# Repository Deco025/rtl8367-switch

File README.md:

# RTL8367 Switch

**RTL8367RB 五口千兆非网管交换机**

> An open-source five-port gigabit Ethernet switch built around the Realtek RTL8367RB. It is unmanaged: the
> chip boots from strap pins and needs no MCU. Each port has a discrete Pulse H5007NL magnetics module, a shielded RJ45
> and two status LEDs. A 12 V input feeds two on-board bucks, 3.3 V (TPS54331) and 1.1 V (TPS62130A).
> The board is a compact 100 × 72 mm, 4-layer KiCad 10 design, assembled on both sides, with complete fabrication
> outputs.

| 正面（网口一侧） | 背面（电源一侧） |
|---|---|
|  |  |

### PCB 走线

| 顶层 F.Cu | 底层 B.Cu（从背面看） |
|---|---|
|  |  |

第 2 层整层是地，第 3 层是电源分区；图里只画了两个外层。

### 前代样机

这是本设计的前代样机，已经搭建并通电运行，图中两个网口接线后链路灯亮起。v0.1 在它的基础上重新设计，网络变压器从 JXD G2401S 换成了 Pulse H5007NL。上面的渲染图和走线图都是 v0.1。

---

## 目录

- [主要指标](#主要指标)
- [系统结构](#系统结构)
- [仓库结构](#仓库结构)
- [打开工程](#打开工程)
- [打样与装配](#打样与装配)
- [设计要点](#设计要点)
- [设计检查与装配注意事项](#设计检查与装配注意事项)
- [许可证](#许可证)
- [致谢](#致谢)

## 主要指标

| 项 | 值 |
|---|---|
| 交换芯片 | Realtek RTL8367RB-VB-CG（LQFP-128，带散热焊盘） |
| 端口 | 5 × 10/100/1000BASE-T，RJ45 带屏蔽壳 |
| 管理 | 非网管，靠 strap 引脚配置；预留 SMI 调试口（J251）和 EEPROM 位置（默认不贴） |
| 网络变压器 | Pulse H5007NL × 5（每口一颗，分立） |
| 指示灯 | 每口一绿一黄，外加一颗电源灯 |
| 输入 | 12 V DC，5.5 × 2.1 mm 插座（CUI PJ-102AH） |
| 输入保护 | 自恢复保险丝 0.75 A（1812L075/33DR）、防反接肖特基 SS34、TVS SMBJ15A |
| 3.3 V | TPS54331 降压，6.8 µH，SS34 续流 |
| 1.1 V（芯片核心） | TPS62130A 降压，2.2 µH，放在背面，紧靠芯片 |
| 复位 | TPS3808G30 监控 3.3 V，带手动复位按键 |
| 时钟 | 25 MHz 晶体 |
| PCB | 100 × 72 mm，4 层，1.58 mm，嘉立创叠层 JLC04161H-3313A（外层 1 oz，内层 0.5 oz） |
| 装配 | 双面贴片：正面 56 个、背面 129 个，共 185 个 |

## 系统结构

```mermaid
flowchart LR
    DC[12 V 输入<br/>保险丝 · 防反接 · TVS] --> B1[TPS54331<br/>3.3 V]
    B1 --> B2[TPS62130A<br/>1.1 V 核心]
    B1 --> FB[磁珠滤波<br/>3.3 V / 1.1 V 模拟与 PLL]
    B1 --> RST[TPS3808<br/>复位监控]
    B2 --> SW
    FB --> SW
    RST --> SW
    X[25 MHz 晶体] --> SW[RTL8367RB<br/>5 口千兆交换]
    SW -- MDI × 4 对 --> T[H5007NL × 5<br/>网络变压器]
    T --> J[RJ45 × 5<br/>Bob Smith 终端到 CHASSIS]
    SW --> LED[LED × 10]
```

- 5 个网口都用芯片内置的 PHY，MDI 从芯片直连变压器，中间没有其他器件。
- 变压器芯片侧的中心抽头各接 0.1 µF 到地，另外预留一个 0 Ω 到 +3V3A 的位置（默认不贴）。
- 线缆侧中心抽头各经 75 Ω 汇到一点，再经 1 nF / 2 kV 接屏蔽地 CHASSIS（Bob Smith 终端）。CHASSIS 与 GND 之间有一颗 1 nF 电容。
- 每对差分线旁预留了 ESD 保护（TPD4E02B04，默认不贴）。

更完整的说明见 [docs/design.md](docs/design.md)。

## 仓库结构

```
.
├── rtl8367-switch.kicad_pro   KiCad 工程
├── *.kicad_sch                原理图：根页 + 电源、芯片供电、芯片控制、5 个网口
├── rtl8367-switch.kicad_pcb   PCB
├── lib/                       工程自带的符号和封装（RTL8367RB、H5007NL、RJ45）
├── fab/                       生产文件（Gerber zip、BOM、坐标、装配图、DRC 报告）
├── 3dmodels/                  第三方 3D 模型的来源清单（模型文件不随仓库分发）
├── docs/
│   ├── design.md              设计说明
│   └── schematics/            原理图 PDF（不装 KiCad 也能看）
├── images/                    渲染图和走线图
├── CHANGELOG.md
└── LICENSE                    CERN-OHL-S-2.0
```

## 打开工程

1. 安装 [KiCad](https://www.kicad.org/) **10.0** 或更新版本。
2. 打开 `rtl8367-switch.kicad_pro`。RTL8367RB、H5007NL 和 RJ45 的符号与封装在 `lib/` 里，工程的库表已经指向它们；其余来自 KiCad 官方库。
3. **3D 模型（可选）**：有 6 种器件的 3D 模型不在 KiCad 官方库里，版权也不允许随仓库再分发。按 [3dmodels/README.md](3dmodels/README.md) 下载到 `3dmodels/`，3D 查看器（`Alt+3`）里就能看到完整外观。不下载也不影响原理图、PCB 和生产文件。

## 打样与装配

生产文件已经导出好，坐标原点在板的左上角：

| 用途 | 文件 |
|---|---|
| 上传给板厂 | [`fab/rtl8367-switch-gerber.zip`](fab/rtl8367-switch-gerber.zip) |
| 物料清单 | [`fab/rtl8367-switch-bom.csv`](fab/rtl8367-switch-bom.csv) |
| 贴片坐标（两面） | [`fab/rtl8367-switch-pos.csv`](fab/rtl8367-switch-pos.csv) |
| 装配图（第 1 页正面，第 2 页背面镜像） | [`fab/rtl8367-switch-assembly.pdf`](fab/rtl8367-switch-assembly.pdf) |
| 下单参数 | [`fab/README.md`](fab/README.md) |

下单要点：

- 4 层，1.6 mm，FR4，**叠层选 JLC04161H-3313A**。差分线的线宽线距是按这个叠层算的 100 Ω，换叠层要重算。
- 最小线宽 / 线距 0.2 / 0.15 mm，过孔 0.45 / 0.3 mm 和 0.6 / 0.3 mm。U102 封装自带 0.2 mm 的散热孔，请确认板厂能做。
- 双面贴片，背面也有器件（大多是去耦电容和上下拉电阻）。
- 变压器之后（线缆侧）的地和电源平面是有意挖空的，保证隔离间距，不要让板厂“补铜”。
- 为了版面整洁，丝印上放不下的一些小阻容位号只保留在装配层（Fab），焊接时请对照装配图。

## 设计要点

- **MDI 直通**：变压器的通道在原理图里重新分配过，芯片到变压器的 20 对差分线全部在顶层直走，不打孔、不交叉，下面是完整的地层。线对的顺序和极性调整放在变压器之后、网口下方那一小段。千兆和 10M 模式下，芯片会自动纠正极性；100M 模式对极性不敏感。
- **电源分区**：第 3 层在芯片下方分成 1.1 V 核心、1.1 V 模拟、3.3 V 模拟几块，其余是 3.3 V 主电源；1.1 V PLL 经磁珠单独供电。每个电源脚旁打一个过孔，直通背面的去耦电容。
- **两个降压电源分开放**：3.3 V 在正面右后角，开关节点铜皮只包芯片 SW 脚、续流二极管和电感，离最近的差分线约 4.6 mm；1.1 V 在背面，紧挨芯片，输入环路（PVIN–C112–PGND）在背面就地闭合，输出经过孔直接进第 3 层的核心电源区。两路的反馈分压器和各自的开关节点之间都隔着两层平面。
- **隔离与屏蔽**：变压器之后（线缆侧）不铺地和电源平面，四个线对分走四层，和芯片侧之间留隔离带；网口屏蔽壳和 Bob Smith 终端单独接 CHASSIS 铺铜。外层地铺铜与差分线保持间距，并用缝合过孔连到地层。

详见 [docs/design.md](docs/design.md)。

## 设计检查与装配注意事项

原理图 ERC 0，PCB DRC 0 错误、0 未连接，原理图与 PCB 一致。装配和调试时请留意：

1. **芯片侧中心抽头**：默认每个抽头接 0.1 µF 到地，同时预留了接 +3V3A 的 0 Ω 位置（接法参考同厂 RTL8211E 的布局指南），可按需要切换。
2. **默认转发配置和 LED 功能**由 strap 决定，可以通过 J251 的 SMI 口读写寄存器确认和调整。
3. **RJ45 的 1 脚方向**请在焊接前对照实物核对。
4. **绿色 LED** 正向压降约 2.8 V，470 Ω 限流下约 1 mA；想要更亮可以减小限流电阻。
5. **复位门限**为 2.79 V，偏低的门限用于避免上电时卡在复位里。
6. **DC 插座**（CUI PJ-102AH）请在下单前按厂家规格书确认货源和额定值。

欢迎提交 Issue 反馈问题或改进建议。

## 许可证

本项目的硬件设计文件（原理图、PCB、生产文件、文档）采用
**[CERN Open Hardware Licence Version 2 – Strongly Reciprocal (CERN-OHL-S-2.0)](LICENSE)**。

简单说：可以自由使用、学习、修改、生产和销售；但如果你发布修改后的设计，或者销售基于它的产品，必须用同样的许可证公开对应的设计源文件。

第三方封装、符号和 3D 模型各自遵循其原始许可，不在本许可证范围内。

## 致谢

- [KiCad](https://www.kicad.org/) 及其官方符号 / 封装 / 3D 库。
- 器件 3D 模型的来源见 [3dmodels/SOURCES.md](3dmodels/SOURCES.md)。

欢迎通过 Issue 反馈问题或提出改进。

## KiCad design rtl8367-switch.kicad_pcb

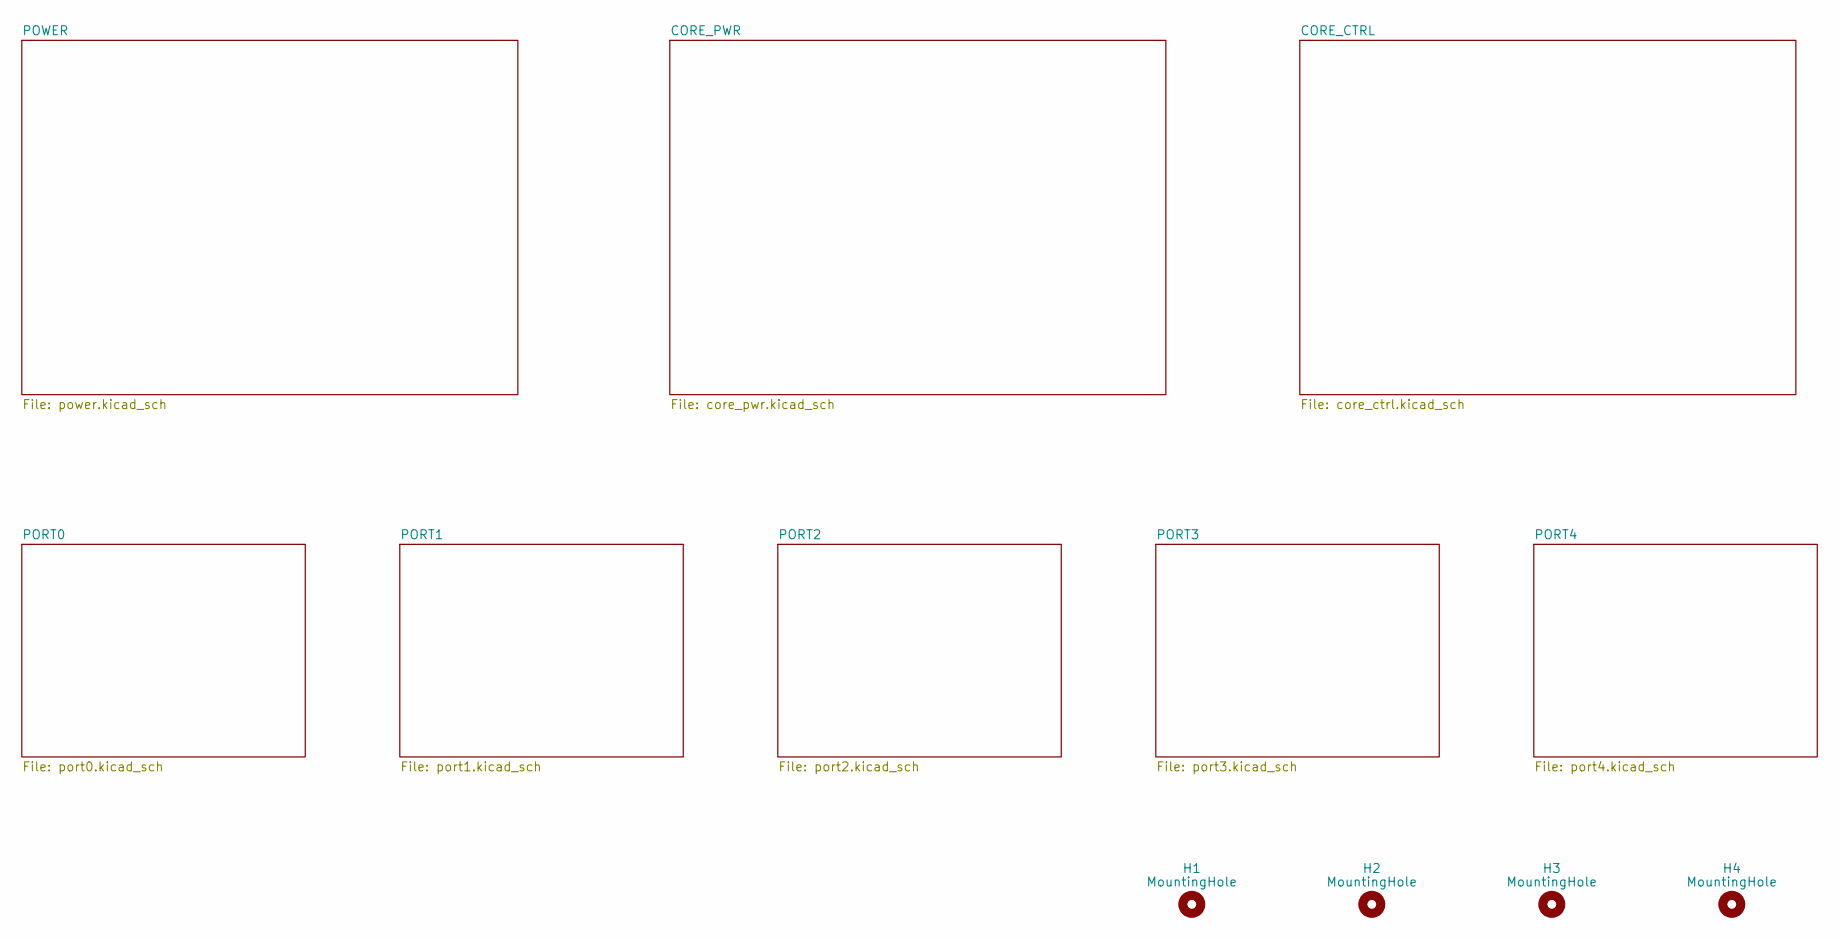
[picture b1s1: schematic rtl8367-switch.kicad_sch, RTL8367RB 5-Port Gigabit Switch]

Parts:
H1, H2, H3, H4: MountingHole; MountingHole_3.2mm_M3

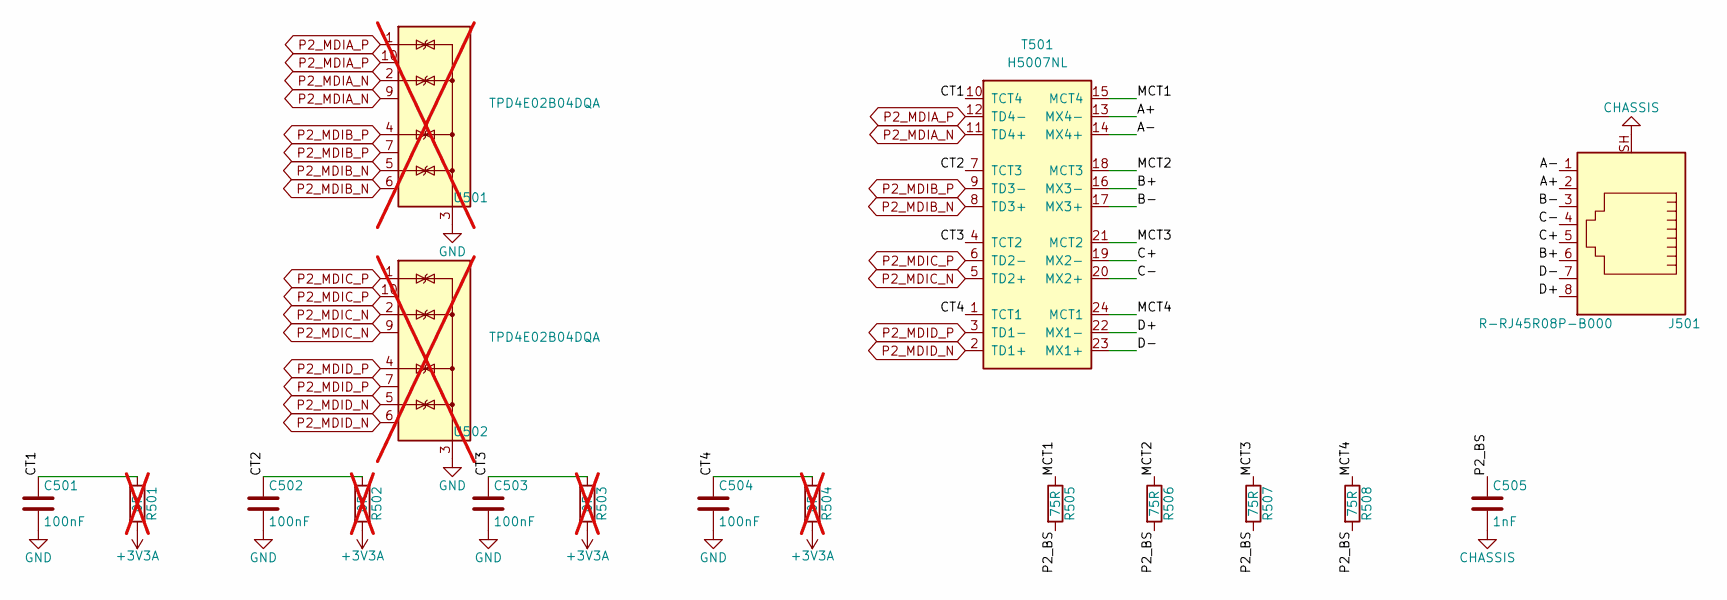
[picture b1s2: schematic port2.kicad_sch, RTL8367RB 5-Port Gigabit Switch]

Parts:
C501, C502, C503, C504: 100nF; C_0402_1005Metric; Voltage 16V
C505: 1nF; C_1206_3216Metric; Voltage 2kV
J501: R-RJ45R08P-B000; RJ45_Ckmtw_R-RJ45R08P-B000_Horizontal; MPN R-RJ45R08P-B000; LCSC C386756
R501, R502, R503, R504: 0R; R_0402_1005Metric; not fitted
R505, R506, R507, R508: 75R; R_0603_1608Metric; Tolerance 1%
T501: H5007NL; Pulse_H5007NL; MPN H5007NL; LCSC C6384935
U501, U502: TPD4E02B04DQA; USON-10_2.5x1.0mm_P0.5mm; MPN TPD4E02B04DQAR; not fitted

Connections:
+3V3A: R501.2, R502.2, R503.2, R504.2; also elsewhere on the board
/PORT2/A+: J501.2, T501.13 (MX4-)
/PORT2/A-: J501.1, T501.14 (MX4+)
/PORT2/B+: J501.6, T501.16 (MX3-)
/PORT2/B-: J501.3, T501.17 (MX3+)
/PORT2/C+: J501.5, T501.19 (MX2-)
/PORT2/C-: J501.4, T501.20 (MX2+)
/PORT2/CT1: C501.1, R501.1, T501.10 (TCT4)
/PORT2/CT2: C502.1, R502.1, T501.7 (TCT3)
/PORT2/CT3: C503.1, R503.1, T501.4 (TCT2)
/PORT2/CT4: C504.1, R504.1, T501.1 (TCT1)
/PORT2/D+: J501.8, T501.22 (MX1-)
/PORT2/D-: J501.7, T501.23 (MX1+)
/PORT2/MCT1: R505.1, T501.15 (MCT4)
/PORT2/MCT2: R506.1, T501.18 (MCT3)
/PORT2/MCT3: R507.1, T501.21 (MCT2)
/PORT2/MCT4: R508.1, T501.24 (MCT1)
/PORT2/P2_BS: C505.1, R505.2, R506.2, R507.2, R508.2
CHASSIS: C505.2, J501.SH; also elsewhere on the board
GND: C501.2, C502.2, C503.2, C504.2, U501.3 (G), U501.8 (G), U502.3 (G), U502.8 (G); also elsewhere on the board
P2_MDIA_N: T501.11 (TD4+), U501.2 (IO2), U501.9 (NC); also elsewhere on the board
P2_MDIA_P: T501.12 (TD4-), U501.1 (IO1), U501.10 (NC); also elsewhere on the board
P2_MDIB_N: T501.8 (TD3+), U501.5 (IO4), U501.6 (NC); also elsewhere on the board
P2_MDIB_P: T501.9 (TD3-), U501.4 (IO3), U501.7 (NC); also elsewhere on the board
P2_MDIC_N: T501.5 (TD2+), U502.2 (IO2), U502.9 (NC); also elsewhere on the board
P2_MDIC_P: T501.6 (TD2-), U502.1 (IO1), U502.10 (NC); also elsewhere on the board
P2_MDID_N: T501.2 (TD1+), U502.5 (IO4), U502.6 (NC); also elsewhere on the board
P2_MDID_P: T501.3 (TD1-), U502.4 (IO3), U502.7 (NC); also elsewhere on the board

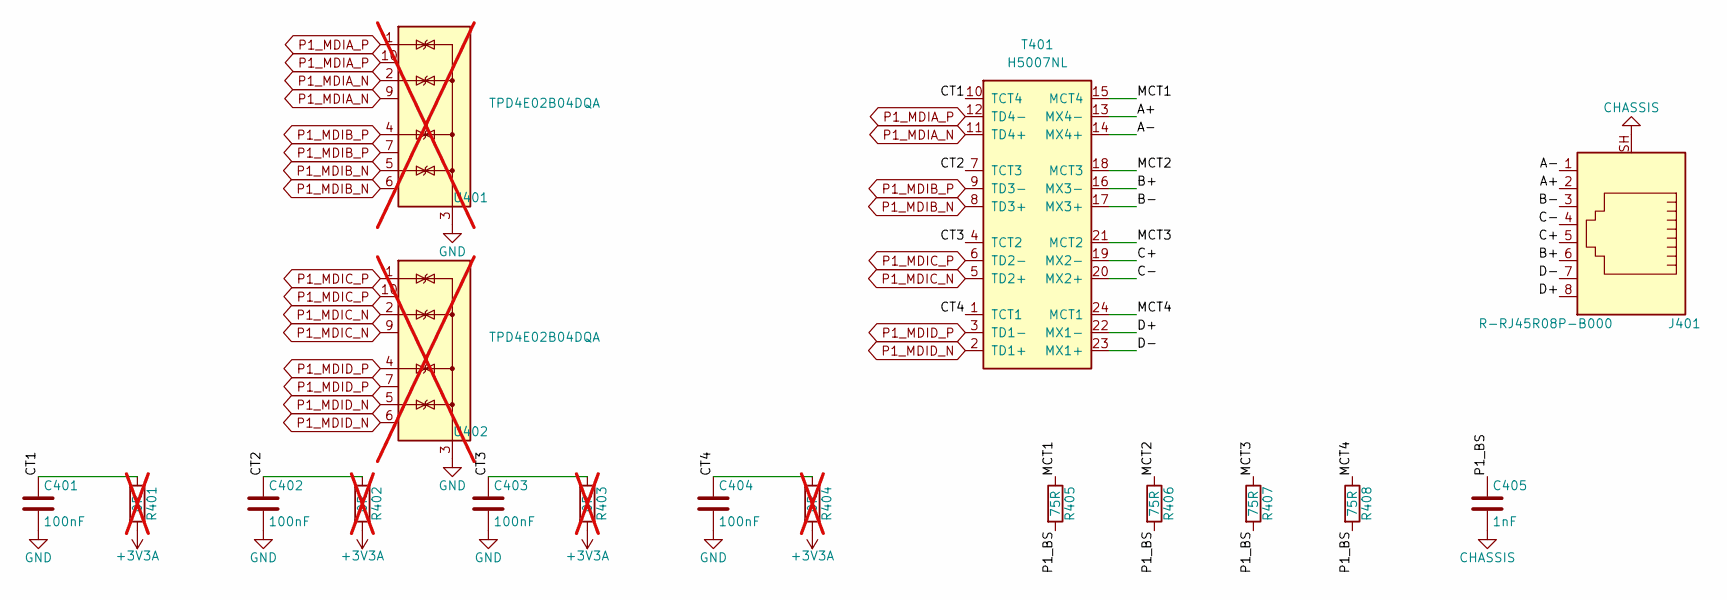
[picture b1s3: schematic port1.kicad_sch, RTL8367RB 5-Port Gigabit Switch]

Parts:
C401, C402, C403, C404: 100nF; C_0402_1005Metric; Voltage 16V
C405: 1nF; C_1206_3216Metric; Voltage 2kV
J401: R-RJ45R08P-B000; RJ45_Ckmtw_R-RJ45R08P-B000_Horizontal; MPN R-RJ45R08P-B000; LCSC C386756
R401, R402, R403, R404: 0R; R_0402_1005Metric; not fitted
R405, R406, R407, R408: 75R; R_0603_1608Metric; Tolerance 1%
T401: H5007NL; Pulse_H5007NL; MPN H5007NL; LCSC C6384935
U401, U402: TPD4E02B04DQA; USON-10_2.5x1.0mm_P0.5mm; MPN TPD4E02B04DQAR; not fitted

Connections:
+3V3A: R401.2, R402.2, R403.2, R404.2; also elsewhere on the board
/PORT1/A+: J401.2, T401.13 (MX4-)
/PORT1/A-: J401.1, T401.14 (MX4+)
/PORT1/B+: J401.6, T401.16 (MX3-)
/PORT1/B-: J401.3, T401.17 (MX3+)
/PORT1/C+: J401.5, T401.19 (MX2-)
/PORT1/C-: J401.4, T401.20 (MX2+)
/PORT1/CT1: C401.1, R401.1, T401.10 (TCT4)
/PORT1/CT2: C402.1, R402.1, T401.7 (TCT3)
/PORT1/CT3: C403.1, R403.1, T401.4 (TCT2)
/PORT1/CT4: C404.1, R404.1, T401.1 (TCT1)
/PORT1/D+: J401.8, T401.22 (MX1-)
/PORT1/D-: J401.7, T401.23 (MX1+)
/PORT1/MCT1: R405.1, T401.15 (MCT4)
/PORT1/MCT2: R406.1, T401.18 (MCT3)
/PORT1/MCT3: R407.1, T401.21 (MCT2)
/PORT1/MCT4: R408.1, T401.24 (MCT1)
/PORT1/P1_BS: C405.1, R405.2, R406.2, R407.2, R408.2
CHASSIS: C405.2, J401.SH; also elsewhere on the board
GND: C401.2, C402.2, C403.2, C404.2, U401.3 (G), U401.8 (G), U402.3 (G), U402.8 (G); also elsewhere on the board
P1_MDIA_N: T401.11 (TD4+), U401.2 (IO2), U401.9 (NC); also elsewhere on the board
P1_MDIA_P: T401.12 (TD4-), U401.1 (IO1), U401.10 (NC); also elsewhere on the board
P1_MDIB_N: T401.8 (TD3+), U401.5 (IO4), U401.6 (NC); also elsewhere on the board
P1_MDIB_P: T401.9 (TD3-), U401.4 (IO3), U401.7 (NC); also elsewhere on the board
P1_MDIC_N: T401.5 (TD2+), U402.2 (IO2), U402.9 (NC); also elsewhere on the board
P1_MDIC_P: T401.6 (TD2-), U402.1 (IO1), U402.10 (NC); also elsewhere on the board
P1_MDID_N: T401.2 (TD1+), U402.5 (IO4), U402.6 (NC); also elsewhere on the board
P1_MDID_P: T401.3 (TD1-), U402.4 (IO3), U402.7 (NC); also elsewhere on the board

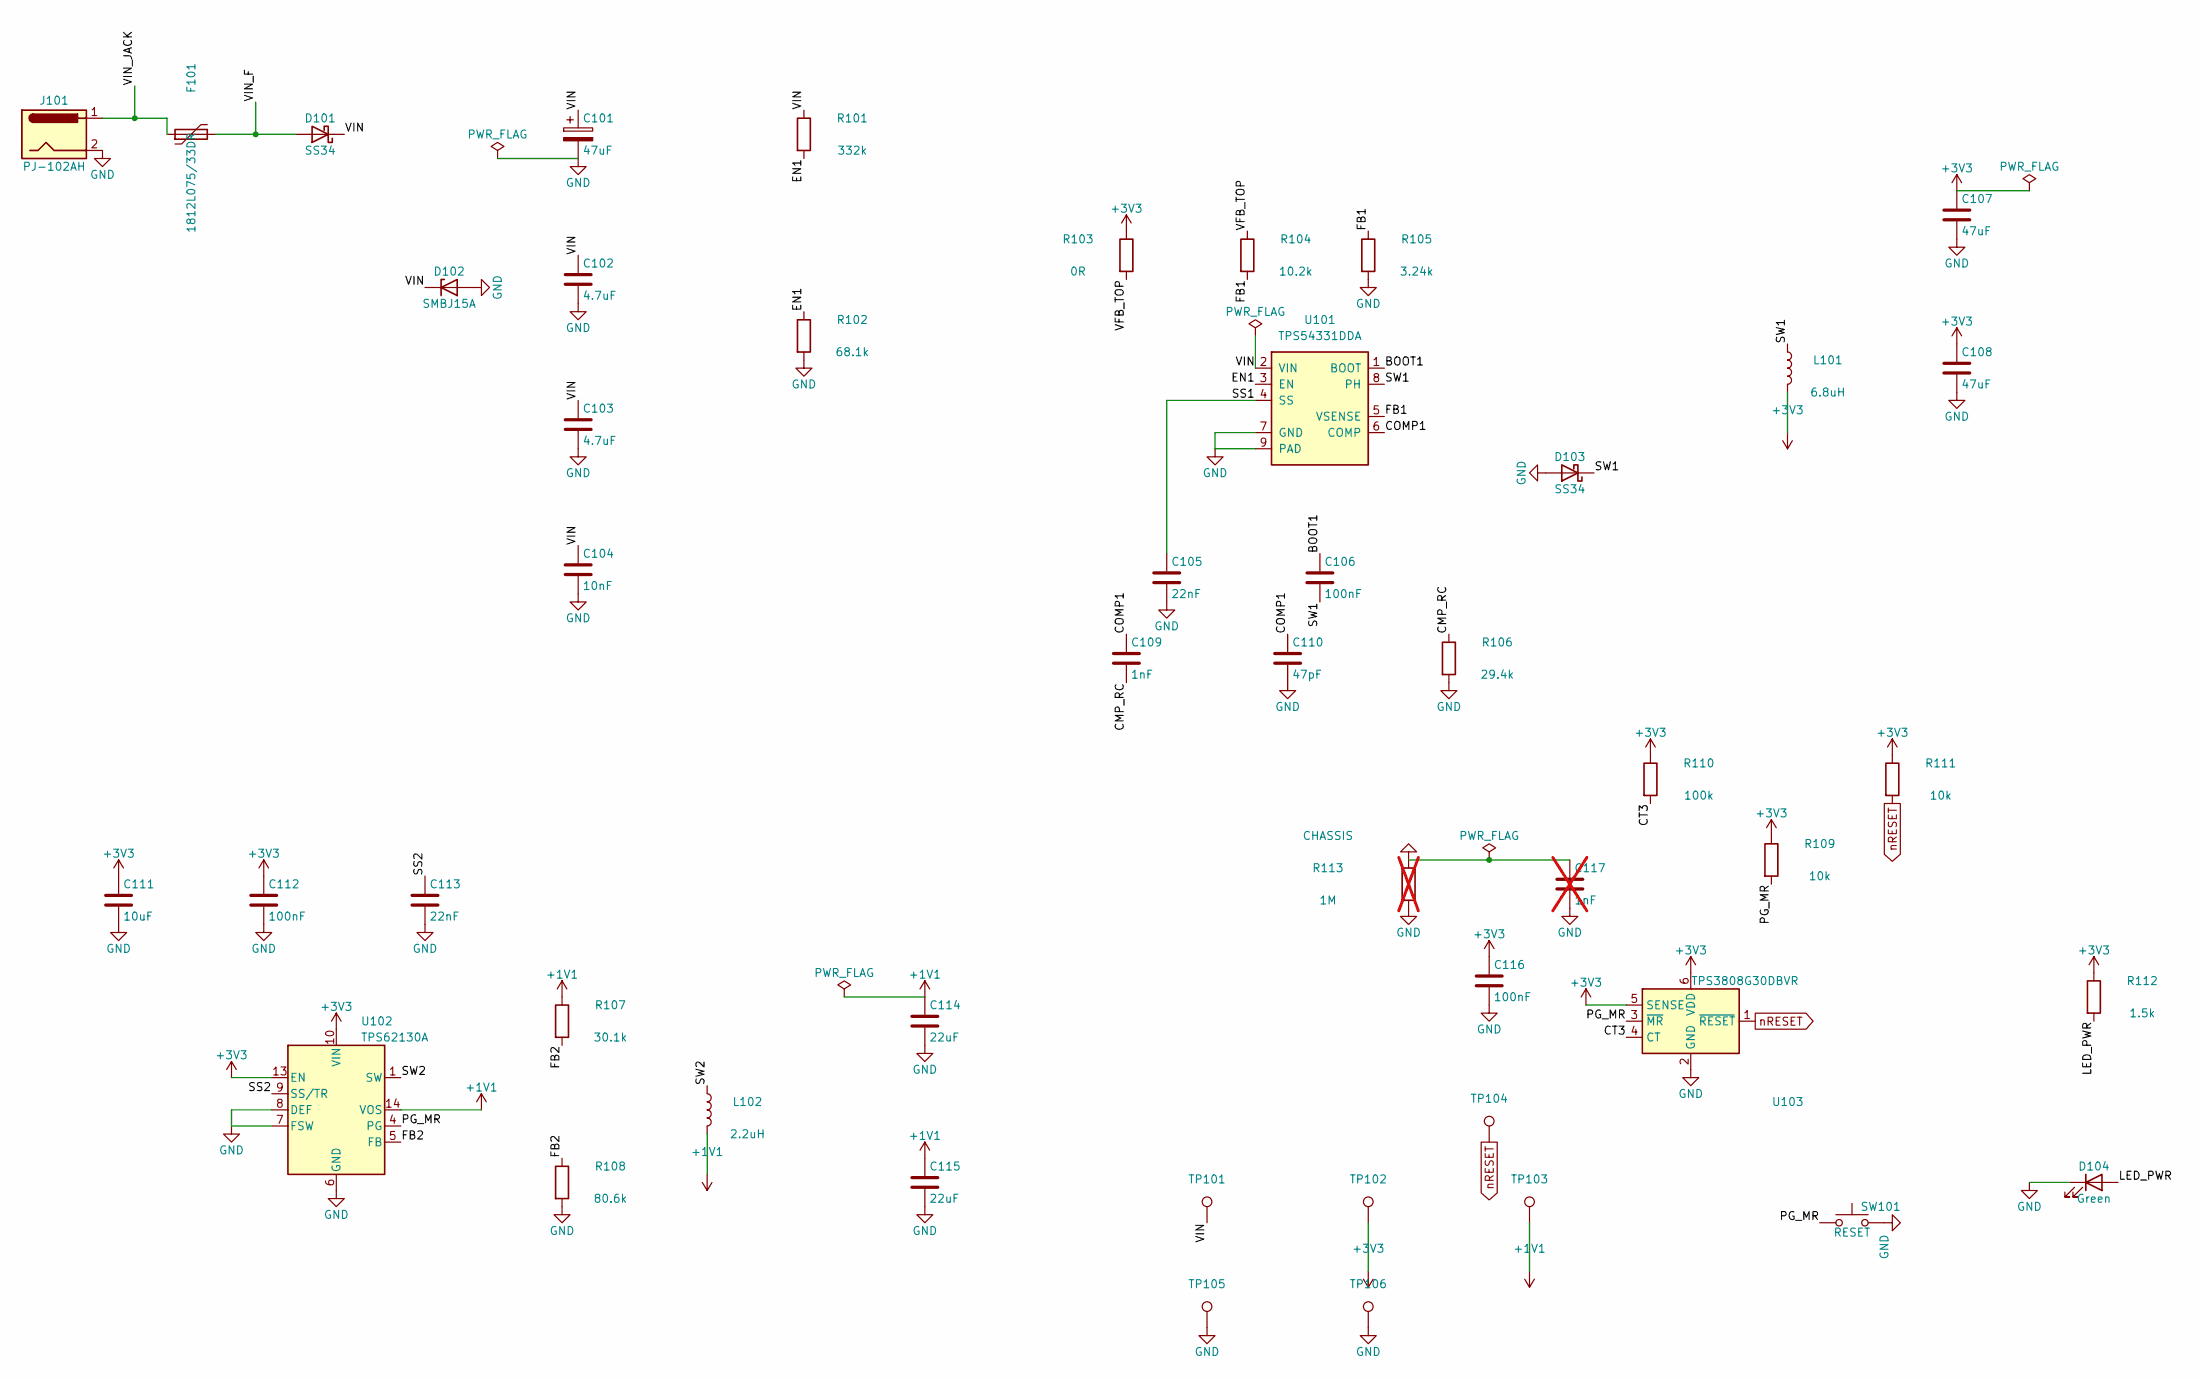
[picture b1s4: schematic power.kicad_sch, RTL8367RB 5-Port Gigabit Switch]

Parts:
C101: 47uF; CP_Elec_6.3x7.7; Voltage 25V
C102, C103: 4.7uF; C_1206_3216Metric; Voltage 25V
C104: 10nF; C_0603_1608Metric; Voltage 50V
C105, C113: 22nF; C_0603_1608Metric; Voltage 16V
C106: 100nF; C_0603_1608Metric; Voltage 50V
C107, C108: 47uF; C_1210_3225Metric; Voltage 10V
C109: 1nF; C_0603_1608Metric; Voltage 50V
C110: 47pF; C_0603_1608Metric; Voltage 50V
C111: 10uF; C_0805_2012Metric; Voltage 10V
C112, C116: 100nF; C_0402_1005Metric; Voltage 16V
C114, C115: 22uF; C_0805_2012Metric; Voltage 6.3V
C117: 1nF; C_1206_3216Metric; Voltage 2kV; not fitted
D101, D103: SS34; D_SMA; MPN SS34; LCSC C8678
D102: SMBJ15A; D_SMB; MPN SMBJ15A; LCSC C83846
D104: Green; LED_0603_1608Metric; MPN LTST-C193TGKT-5A; LCSC C12065
F101: 1812L075/33DR; Fuse_1812_4532Metric; MPN 1812L075/33DR; LCSC C151170
J101: PJ-102AH; BarrelJack_CUI_PJ-102AH_Horizontal; MPN PJ-102AH; LCSC C3096093
L101: 6.8uH; L_Sunlord_SWPA6045S; MPN SWPA6045S6R8MT; LCSC C57254
L102: 2.2uH; L_Sunlord_SWPA4030S; MPN SWPA4030S2R2MT; LCSC C36409
R101: 332k; R_0603_1608Metric; Tolerance 1%
R102: 68.1k; R_0603_1608Metric; Tolerance 1%
R103: 0R; R_0603_1608Metric
R104: 10.2k; R_0603_1608Metric; Tolerance 1%
R105: 3.24k; R_0603_1608Metric; Tolerance 1%
R106: 29.4k; R_0603_1608Metric; Tolerance 1%
R107: 30.1k; R_0402_1005Metric; Tolerance 1%
R108: 80.6k; R_0402_1005Metric; Tolerance 1%
R109, R111: 10k; R_0402_1005Metric
R110: 100k; R_0402_1005Metric
R112: 1.5k; R_0402_1005Metric
R113: 1M; R_0603_1608Metric; not fitted
SW101: RESET; SW_Push_1P1T_XKB_TS-1187A; MPN TS-1187A-B-A-B; LCSC C318884
TP101: VIN; TestPoint_Pad_D1.5mm
TP102: +3V3; TestPoint_Pad_D1.5mm
TP103: +1V1; TestPoint_Pad_D1.5mm
TP104: nRESET; TestPoint_Pad_D1.5mm
TP105, TP106: GND; TestPoint_Pad_D1.5mm
U101: TPS54331DDA; Texas_HSOP-8-1EP_3.9x4.9mm_P1.27mm_ThermalVias; MPN TPS54331DDAR; LCSC C90761
U102: TPS62130A; VQFN-16-1EP_3x3mm_P0.5mm_EP1.68x1.68mm_ThermalVias; MPN TPS62130ARGTR; LCSC C337502
U103: TPS3808G30DBVR; SOT-23-6; MPN TPS3808G30DBVR; LCSC C189211

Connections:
+1V1: C114.1, C115.1, L102.2, R107.1, TP103.1, U102.14 (VOS); also elsewhere on the board
+3V3: C107.1, C108.1, C111.1, C112.1, C116.1, L101.2, R103.1, R109.1, R110.1, R111.1, R112.1, TP102.1, U102.10 (VIN), U102.11 (VIN), U102.12 (VIN), U102.13 (EN), U103.5 (SENSE), U103.6 (VDD); also elsewhere on the board
/POWER/BOOT1: C106.1, U101.1 (BOOT)
/POWER/CMP_RC: C109.2, R106.1
/POWER/COMP1: C109.1, C110.1, U101.6 (COMP)
/POWER/CT3: R110.2, U103.4 (CT)
/POWER/EN1: R101.2, R102.1, U101.3 (EN)
/POWER/FB1: R104.2, R105.1, U101.5 (VSENSE)
/POWER/FB2: R107.2, R108.1, U102.5 (FB)
/POWER/LED_PWR: D104.2 (A), R112.2
/POWER/PG_MR: R109.2, SW101.1, U102.4 (PG), U103.3 (~MR)
/POWER/SS1: C105.1, U101.4 (SS)
/POWER/SS2: C113.1, U102.9 (SS/TR)
/POWER/SW1: C106.2, D103.1 (K), L101.1, U101.8 (PH)
/POWER/SW2: L102.1, U102.1 (SW), U102.2 (SW), U102.3 (SW)
/POWER/VFB_TOP: R103.2, R104.1
/POWER/VIN: C101.1, C102.1, C103.1, C104.1, D101.1 (K), D102.1 (K), R101.1, TP101.1, U101.2 (VIN)
/POWER/VIN_F: D101.2 (A), F101.2
/POWER/VIN_JACK: F101.1, J101.1
CHASSIS: C117.1, R113.1; also elsewhere on the board
GND: C101.2, C102.2, C103.2, C104.2, C105.2, C107.2, C108.2, C110.2, C111.2, C112.2, C113.2, C114.2, C115.2, C116.2, C117.2, D102.2 (A), D103.2 (A), D104.1 (K), J101.2, R102.2, R105.2, R106.2, R108.2, R113.2, SW101.2, TP105.1, TP106.1, U101.7 (GND), U101.9 (PAD), U102.6 (GND), U102.7 (FSW), U102.8 (DEF), U102.15 (GND), U102.16 (GND), U102.17 (GND), U103.2 (GND); also elsewhere on the board
nRESET: R111.2, TP104.1, U103.1 (~RESET); also elsewhere on the board

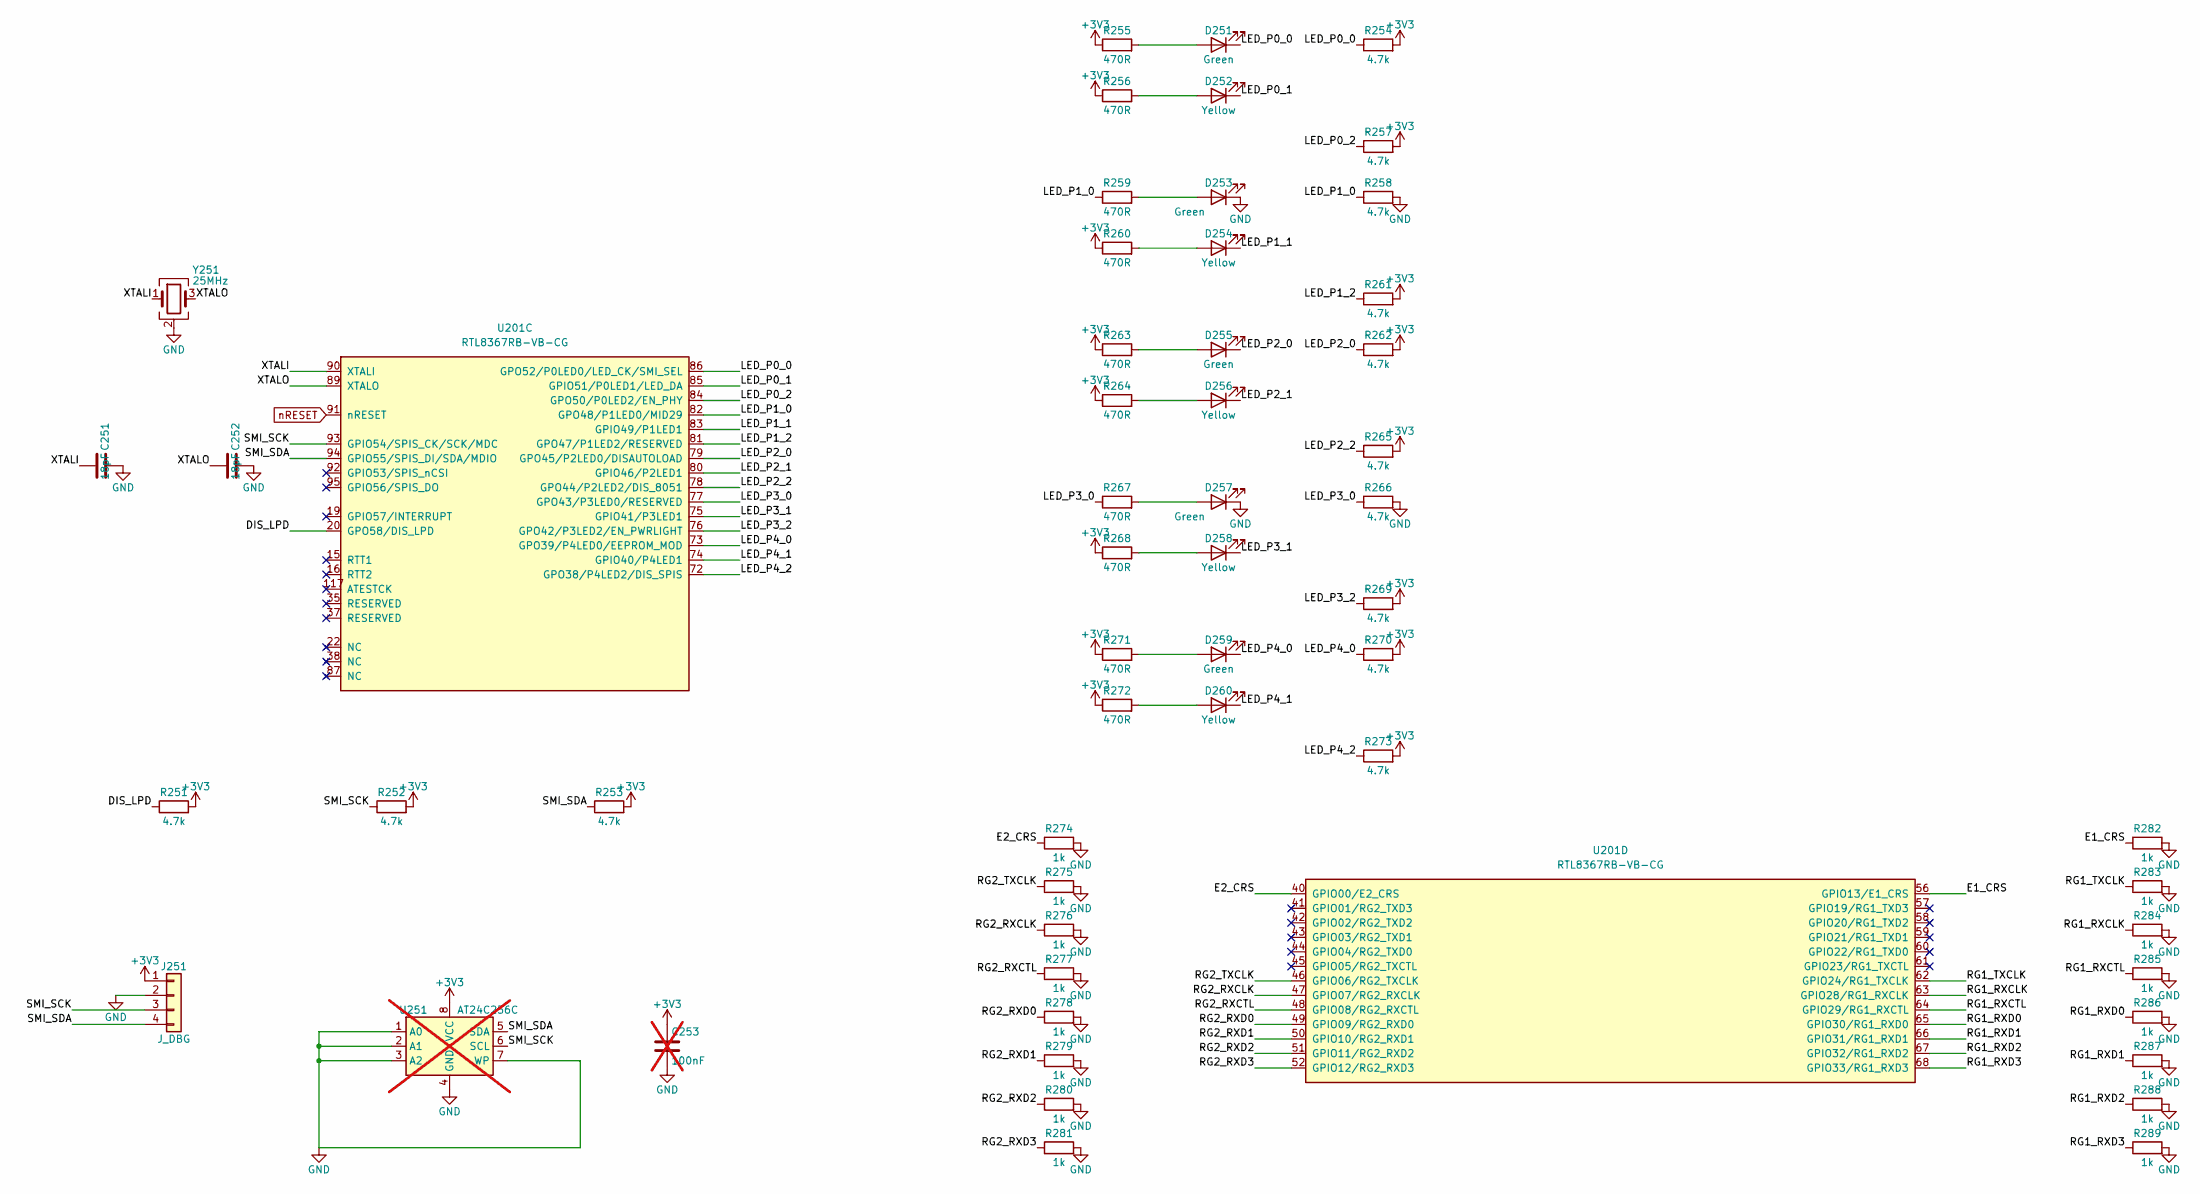
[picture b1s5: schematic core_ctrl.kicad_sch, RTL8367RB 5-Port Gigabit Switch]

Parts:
C251, C252: 18pF; C_0402_1005Metric; Voltage 50V
C253: 100nF; C_0402_1005Metric; Voltage 16V; not fitted
D251, D253, D255, D257, D259: Green; LED_0603_1608Metric; MPN LTST-C193TGKT-5A; LCSC C12065
D252, D254, D256, D258, D260: Yellow; LED_0603_1608Metric; MPN KT-0603Y; LCSC C2287
J251: J_DBG; PinHeader_1x04_P2.54mm_Vertical
R251, R252, R253, R254, R257, R258, R261, R262, R265, R266, R269, R270, R273: 4.7k; R_0402_1005Metric
R255, R256, R259, R260, R263, R264, R267, R268, R271, R272: 470R; R_0402_1005Metric
R274, R275, R276, R277, R278, R279, R280, R281, R282, R283, R284, R285, R286, R287, R288, R289: 1k; R_0402_1005Metric
U201: RTL8367RB-VB-CG; LQFP-128-1EP_14x14mm_P0.4mm_EP5.5x5.5mm_ThermalVias; MPN RTL8367RB-VB-CG; LCSC C2761412
U251: AT24C256C; SOIC-8_3.9x4.9mm_P1.27mm; MPN AT24C256C-SSHL-T; LCSC C6482; not fitted
Y251: 25MHz; Crystal_SMD_3225-4Pin_3.2x2.5mm; MPN X322525MOB4SI; LCSC C9006

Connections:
+3V3: C253.1, J251.1, R251.2, R252.2, R253.2, R254.2, R255.1, R256.1, R257.2, R260.1, R261.2, R262.2, R263.1, R264.1, R265.2, R268.1, R269.2, R270.2, R271.1, R272.1, R273.2, U251.8 (VCC); also elsewhere on the board
/CORE_CTRL/DIS_LPD: R251.1, U201.20 (GPO58/DIS_LPD)
/CORE_CTRL/E1_CRS: R282.1, U201.56 (GPIO13/E1_CRS)
/CORE_CTRL/E2_CRS: R274.1, U201.40 (GPIO00/E2_CRS)
/CORE_CTRL/LED_P0_0: D251.1 (K), R254.1, U201.86 (GPO52/P0LED0/LED_CK/SMI_SEL)
/CORE_CTRL/LED_P0_1: D252.1 (K), U201.85 (GPIO51/P0LED1/LED_DA)
/CORE_CTRL/LED_P0_2: R257.1, U201.84 (GPO50/P0LED2/EN_PHY)
/CORE_CTRL/LED_P1_0: R258.1, R259.1, U201.82 (GPO48/P1LED0/MID29)
/CORE_CTRL/LED_P1_1: D254.1 (K), U201.83 (GPIO49/P1LED1)
/CORE_CTRL/LED_P1_2: R261.1, U201.81 (GPO47/P1LED2/RESERVED)
/CORE_CTRL/LED_P2_0: D255.1 (K), R262.1, U201.79 (GPO45/P2LED0/DISAUTOLOAD)
/CORE_CTRL/LED_P2_1: D256.1 (K), U201.80 (GPIO46/P2LED1)
/CORE_CTRL/LED_P2_2: R265.1, U201.78 (GPO44/P2LED2/DIS_8051)
/CORE_CTRL/LED_P3_0: R266.1, R267.1, U201.77 (GPO43/P3LED0/RESERVED)
/CORE_CTRL/LED_P3_1: D258.1 (K), U201.75 (GPIO41/P3LED1)
/CORE_CTRL/LED_P3_2: R269.1, U201.76 (GPO42/P3LED2/EN_PWRLIGHT)
/CORE_CTRL/LED_P4_0: D259.1 (K), R270.1, U201.73 (GPO39/P4LED0/EEPROM_MOD)
/CORE_CTRL/LED_P4_1: D260.1 (K), U201.74 (GPIO40/P4LED1)
/CORE_CTRL/LED_P4_2: R273.1, U201.72 (GPO38/P4LED2/DIS_SPIS)
/CORE_CTRL/RG1_RXCLK: R284.1, U201.63 (GPIO28/RG1_RXCLK)
/CORE_CTRL/RG1_RXCTL: R285.1, U201.64 (GPIO29/RG1_RXCTL)
/CORE_CTRL/RG1_RXD0: R286.1, U201.65 (GPIO30/RG1_RXD0)
/CORE_CTRL/RG1_RXD1: R287.1, U201.66 (GPIO31/RG1_RXD1)
/CORE_CTRL/RG1_RXD2: R288.1, U201.67 (GPIO32/RG1_RXD2)
/CORE_CTRL/RG1_RXD3: R289.1, U201.68 (GPIO33/RG1_RXD3)
/CORE_CTRL/RG1_TXCLK: R283.1, U201.62 (GPIO24/RG1_TXCLK)
/CORE_CTRL/RG2_RXCLK: R276.1, U201.47 (GPIO07/RG2_RXCLK)
/CORE_CTRL/RG2_RXCTL: R277.1, U201.48 (GPIO08/RG2_RXCTL)
/CORE_CTRL/RG2_RXD0: R278.1, U201.49 (GPIO09/RG2_RXD0)
/CORE_CTRL/RG2_RXD1: R279.1, U201.50 (GPIO10/RG2_RXD1)
/CORE_CTRL/RG2_RXD2: R280.1, U201.51 (GPIO11/RG2_RXD2)
/CORE_CTRL/RG2_RXD3: R281.1, U201.52 (GPIO12/RG2_RXD3)
/CORE_CTRL/RG2_TXCLK: R275.1, U201.46 (GPIO06/RG2_TXCLK)
/CORE_CTRL/SMI_SCK: J251.3, R252.1, U201.93 (GPIO54/SPIS_CK/SCK/MDC), U251.6 (SCL)
/CORE_CTRL/SMI_SDA: J251.4, R253.1, U201.94 (GPIO55/SPIS_DI/SDA/MDIO), U251.5 (SDA)
/CORE_CTRL/XTALI: C251.1, U201.90 (XTALI), Y251.1
/CORE_CTRL/XTALO: C252.1, U201.89 (XTALO), Y251.3
GND: C251.2, C252.2, C253.2, D253.1 (K), D257.1 (K), J251.2, R258.2, R266.2, R274.2, R275.2, R276.2, R277.2, R278.2, R279.2, R280.2, R281.2, R282.2, R283.2, R284.2, R285.2, R286.2, R287.2, R288.2, R289.2, U251.1 (A0), U251.2 (A1), U251.3 (A2), U251.4 (GND), U251.7 (WP), Y251.2 (G), Y251.4 (G); also elsewhere on the board
unnamed: D251.2 (A), R255.2
unnamed: D252.2 (A), R256.2
unnamed: D253.2 (A), R259.2
unnamed: D254.2 (A), R260.2
unnamed: D255.2 (A), R263.2
unnamed: D256.2 (A), R264.2
unnamed: D257.2 (A), R267.2
unnamed: D258.2 (A), R268.2
unnamed: D259.2 (A), R271.2
unnamed: D260.2 (A), R272.2
nRESET: U201.91 (nRESET); also elsewhere on the board

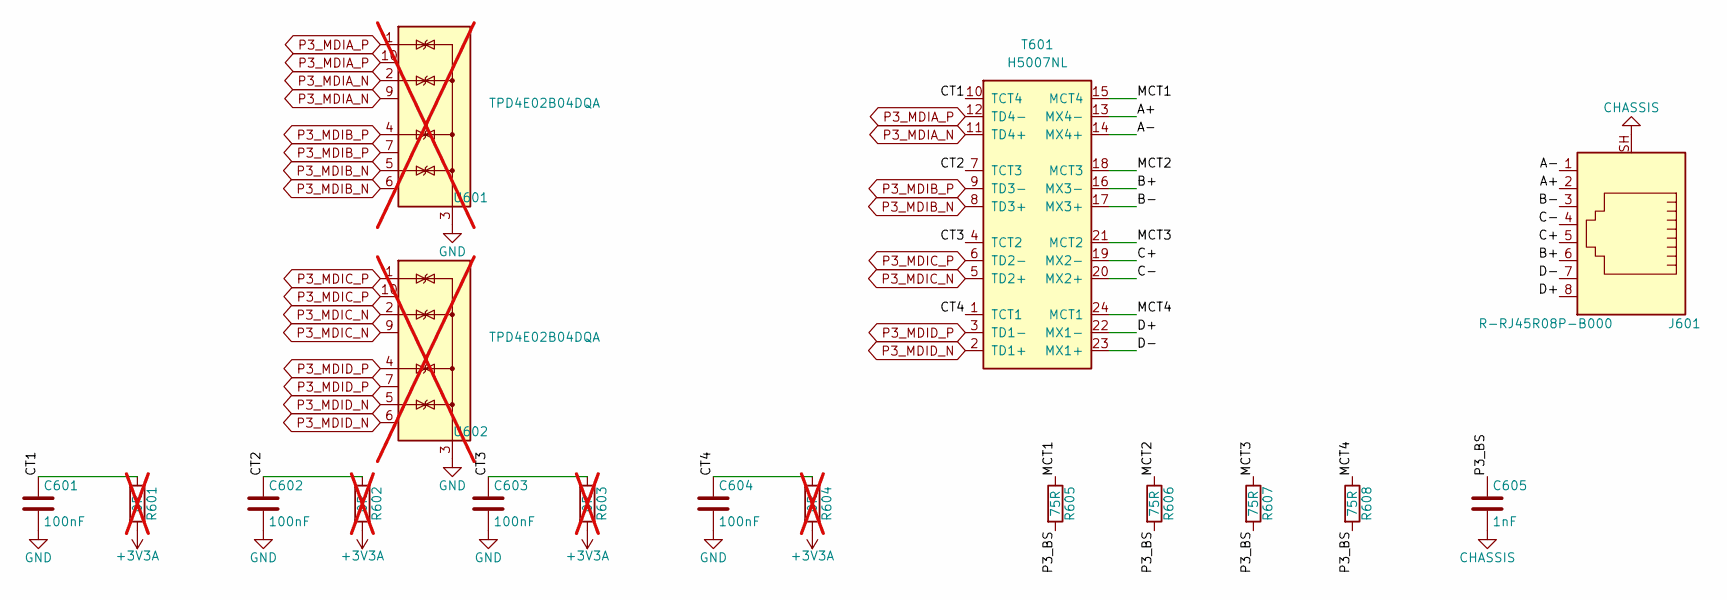
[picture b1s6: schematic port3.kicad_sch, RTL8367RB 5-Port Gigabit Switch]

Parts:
C601, C602, C603, C604: 100nF; C_0402_1005Metric; Voltage 16V
C605: 1nF; C_1206_3216Metric; Voltage 2kV
J601: R-RJ45R08P-B000; RJ45_Ckmtw_R-RJ45R08P-B000_Horizontal; MPN R-RJ45R08P-B000; LCSC C386756
R601, R602, R603, R604: 0R; R_0402_1005Metric; not fitted
R605, R606, R607, R608: 75R; R_0603_1608Metric; Tolerance 1%
T601: H5007NL; Pulse_H5007NL; MPN H5007NL; LCSC C6384935
U601, U602: TPD4E02B04DQA; USON-10_2.5x1.0mm_P0.5mm; MPN TPD4E02B04DQAR; not fitted

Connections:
+3V3A: R601.2, R602.2, R603.2, R604.2; also elsewhere on the board
/PORT3/A+: J601.2, T601.13 (MX4-)
/PORT3/A-: J601.1, T601.14 (MX4+)
/PORT3/B+: J601.6, T601.16 (MX3-)
/PORT3/B-: J601.3, T601.17 (MX3+)
/PORT3/C+: J601.5, T601.19 (MX2-)
/PORT3/C-: J601.4, T601.20 (MX2+)
/PORT3/CT1: C601.1, R601.1, T601.10 (TCT4)
/PORT3/CT2: C602.1, R602.1, T601.7 (TCT3)
/PORT3/CT3: C603.1, R603.1, T601.4 (TCT2)
/PORT3/CT4: C604.1, R604.1, T601.1 (TCT1)
/PORT3/D+: J601.8, T601.22 (MX1-)
/PORT3/D-: J601.7, T601.23 (MX1+)
/PORT3/MCT1: R605.1, T601.15 (MCT4)
/PORT3/MCT2: R606.1, T601.18 (MCT3)
/PORT3/MCT3: R607.1, T601.21 (MCT2)
/PORT3/MCT4: R608.1, T601.24 (MCT1)
/PORT3/P3_BS: C605.1, R605.2, R606.2, R607.2, R608.2
CHASSIS: C605.2, J601.SH; also elsewhere on the board
GND: C601.2, C602.2, C603.2, C604.2, U601.3 (G), U601.8 (G), U602.3 (G), U602.8 (G); also elsewhere on the board
P3_MDIA_N: T601.11 (TD4+), U601.2 (IO2), U601.9 (NC); also elsewhere on the board
P3_MDIA_P: T601.12 (TD4-), U601.1 (IO1), U601.10 (NC); also elsewhere on the board
P3_MDIB_N: T601.8 (TD3+), U601.5 (IO4), U601.6 (NC); also elsewhere on the board
P3_MDIB_P: T601.9 (TD3-), U601.4 (IO3), U601.7 (NC); also elsewhere on the board
P3_MDIC_N: T601.5 (TD2+), U602.2 (IO2), U602.9 (NC); also elsewhere on the board
P3_MDIC_P: T601.6 (TD2-), U602.1 (IO1), U602.10 (NC); also elsewhere on the board
P3_MDID_N: T601.2 (TD1+), U602.5 (IO4), U602.6 (NC); also elsewhere on the board
P3_MDID_P: T601.3 (TD1-), U602.4 (IO3), U602.7 (NC); also elsewhere on the board
